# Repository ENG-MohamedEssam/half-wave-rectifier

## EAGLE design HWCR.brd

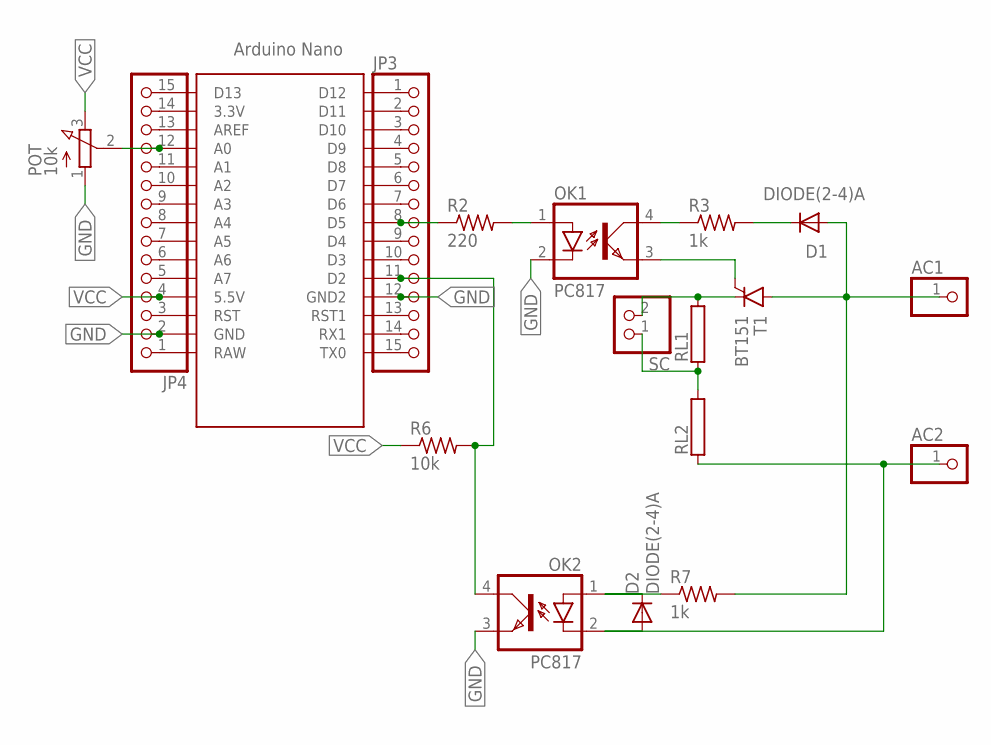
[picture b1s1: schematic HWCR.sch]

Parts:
AC1, AC2: PINHD-1X1; 1X01
D1, D2: DIODE(2-4)A; DO35-10
JP3, JP4: PINHD-1X15; 1X15
OK1, OK2: PC817; DIL04
POT: 10k; 3RP/1610N
R2: 220; 0207/10
R3, R7: 1k; 0207/10
R6: 10k; 0207/10
RL1, RL2: RKP296; KP296
SC: PINHD-1X2; 1X02
T1: BT151; TO220CL
U$1: ARDUINO_NANO; NANO

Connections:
GND: JP3.12, JP4.2, OK1.2 (C), OK2.3 (EMIT), POT.1 (A), U$1.GND, U$1.GND1 (GND2)
unnamed: JP4.12, POT.2 (S), U$1.A0
unnamed: JP3.1, U$1.D12
unnamed: JP3.2, U$1.D11
unnamed: JP3.3, U$1.D10
unnamed: JP3.4, U$1.D9
unnamed: JP3.5, U$1.D8
unnamed: JP3.6, U$1.D7
unnamed: JP3.7, U$1.D6
unnamed: JP3.8, R2.1, U$1.D5
unnamed: JP3.9, U$1.D4
unnamed: JP3.10, U$1.D3
unnamed: JP3.11, OK2.4 (COL), R6.2, U$1.D2
unnamed: OK1.1 (A), R2.2
unnamed: JP3.13, U$1.RST1
unnamed: JP3.14, U$1.RX1
unnamed: JP3.15, U$1.TX0
unnamed: JP4.1, U$1.RAW
unnamed: D1.C, R3.2
unnamed: JP4.3, U$1.RST
unnamed: OK1.4 (COL), R3.1
unnamed: JP4.5, U$1.A7
unnamed: JP4.6, U$1.A6
unnamed: JP4.7, U$1.A5
unnamed: JP4.8, U$1.A4
unnamed: JP4.9, U$1.A3
unnamed: JP4.10, U$1.A2
unnamed: JP4.11, U$1.A1
unnamed: JP4.13, U$1.AREF
unnamed: JP4.14, U$1.3.3V
unnamed: JP4.15, U$1.D13
unnamed: OK1.3 (EMIT), T1.G
unnamed: RL1.1, RL2.2, SC.1
unnamed: RL1.2, SC.2, T1.C
unnamed: AC2.1, D2.A, OK2.2 (C), RL2.1
unnamed: AC1.1, D1.A, R7.2, T1.A
unnamed: D2.C, OK2.1 (A), R7.1
VCC: JP4.4, POT.3 (E), R6.1, U$1.5V (5.5V)

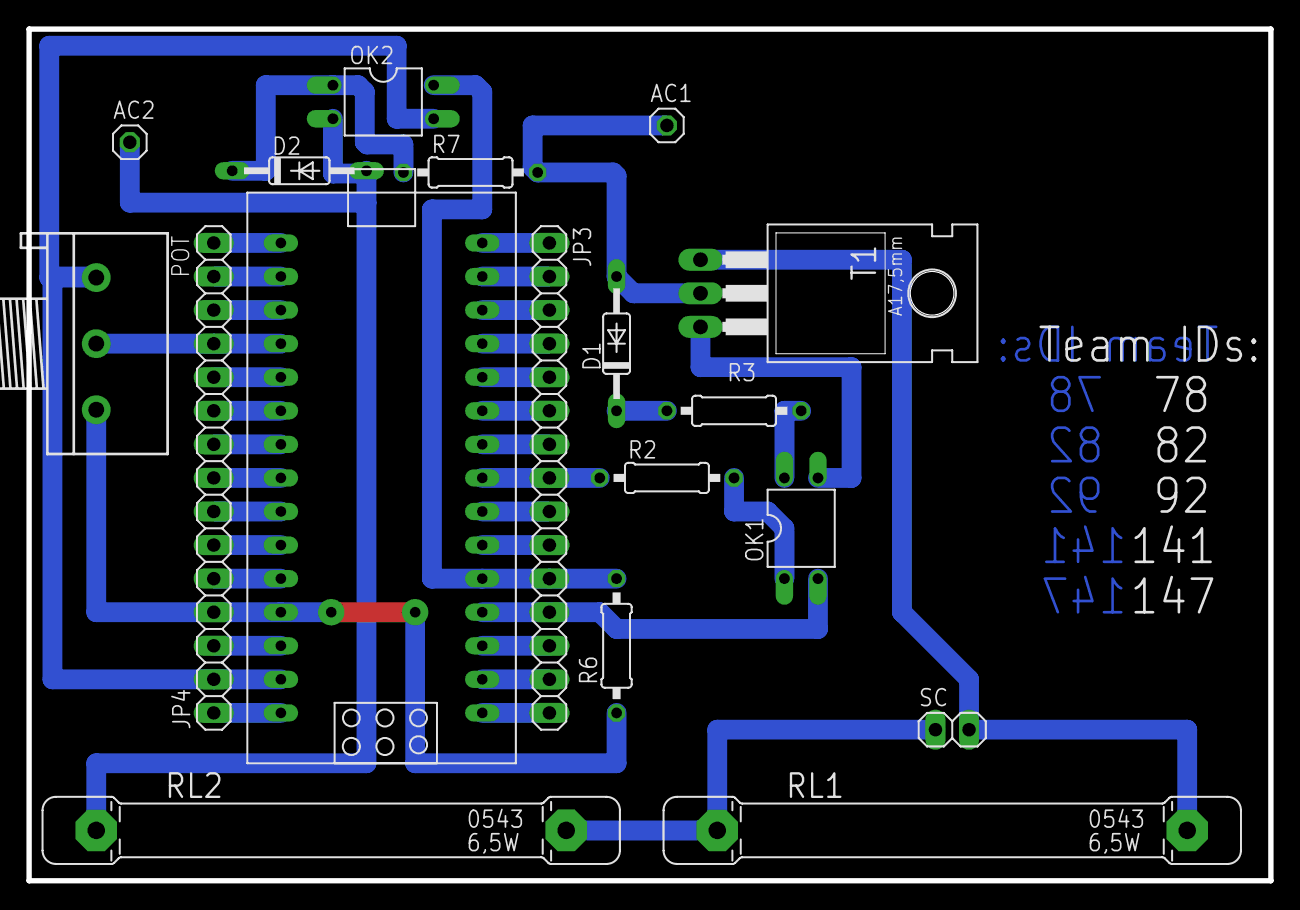
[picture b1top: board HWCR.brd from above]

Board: 2 copper layers, 94.0 x 64.4 mm, 18 parts (0 on the bottom side), 38 nets.
